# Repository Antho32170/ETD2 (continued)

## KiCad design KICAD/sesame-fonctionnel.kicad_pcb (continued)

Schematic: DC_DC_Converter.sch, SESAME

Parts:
C36, C37, C38, C47, C48, C49: 470uF; CP_Radial_D12.5mm_P5.00mm
C39, C40, C41, C42, C43, C44, C45, C46: C; C_0805_2012Metric_Pad1.18x1.45mm_HandSolder
L2: INDUCTOR; Multi-coil
QLP1: TK65G10N1; TO-263-2
QLS1: TK65G10N1; TO-263-2
QRP1: TK65G10N1; TO-263-2
QRS1: TK65G10N1; TO-263-2
R89, R90, R91, R92, R93, R94, R95, R96: R; R_0805_2012Metric_Pad1.20x1.40mm_HandSolder

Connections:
/DC/DC CONVERTER/VD_LS: C36.1, C37.1, C38.1, C39.1, C40.1, C41.1, QLS1.2 (D); also elsewhere on the board
/DC/DC CONVERTER/VG_LP: QLP1.1 (G), R90.1; also elsewhere on the board
/DC/DC CONVERTER/VG_LS: QLS1.1 (G), R89.1; also elsewhere on the board
/DC/DC CONVERTER/VG_RP: QRP1.1 (G), R96.1; also elsewhere on the board
/MOS DRIVER L/VS: C42.1, L2.1, QLP1.2 (D), QLS1.3 (S), R89.2, R91.2; also elsewhere on the board
/MOS DRIVER R/VG_P: QRS1.1 (G), R95.1; also elsewhere on the board
/MOS DRIVER R/VS: C44.1, L2.2, QRP1.2 (D), QRS1.3 (S), R93.2, R95.2; also elsewhere on the board
/U/I SENSOR RIGHT/VD_Mos: C43.1, C45.1, C46.1, C47.1, C48.1, C49.1, QRS1.2 (D); also elsewhere on the board
unnamed: C41.2, R91.1
unnamed: C42.2, R92.1
unnamed: C43.2, R93.1
unnamed: C44.2, R94.1

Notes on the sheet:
Inductor between 90uH -> 125uH https://fr.rs-online.com/web/p/inductances-traversantes/1816037 https://fr.rs-online.com/web/p/inductances-traversantes/1542466 https://fr.rs-online.com/web/p/inductances-traversantes/1048448 https://fr.rs-online.com/web/p/inductances-traversantes/1229231

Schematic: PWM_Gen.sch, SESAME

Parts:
C26: 100n; C_0805_2012Metric_Pad1.18x1.45mm_HandSolder
JP15, JP16, JP17, JP18: Jumper_3_Bridged12; SolderJumper-3_P1.3mm_Bridged12_Pad1.0x1.5mm
R70, R72, R73, R74, R75: 100k; R_0805_2012Metric_Pad1.20x1.40mm_HandSolder
R71: 4.7k; R_0805_2012Metric_Pad1.20x1.40mm_HandSolder
TP35: TP_NOP; TestPoint_THTPad_D2.0mm_Drill1.0mm
TP36, TP37, TP38: TP_POP; TestPoint_Loop_D1.80mm_Drill1.0mm_Beaded
U1, U13: AD8030; SO-8_5.3x6.2mm_P1.27mm

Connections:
/INT_PWM_Power: JP17.2 (C); also elsewhere on the board
/PID/Feedback: JP15.3 (B), JP16.1 (A), R73.2; also elsewhere on the board
/PWM GEN/Feedback_Deadtime: JP15.1 (A), JP16.3 (B), R75.2, TP36.1, U1.7
/PWM GEN/Feedback_Deadtime_Jump: JP15.2 (C), U13.3 (+)
/PWM GEN/Feedback_Jump: JP16.2 (C), U13.6 (-)
/PWM GEN/PWM_Power_Jumper: JP17.1 (A), JP18.3 (B), TP37.1, U13.1
/PWM GEN/Ramp: U13.2 (-), U13.5 (+); also elsewhere on the board
/PWM GEN/VDeadTime: R70.2, R71.1, R72.1, TP35.1
/PWM GEN/~PWM_Freewheel_Jumper: JP17.3 (B), JP18.1 (A), TP38.1, U13.7
/~INT_PWM_Freewheel: JP18.2 (C); also elsewhere on the board
unnamed: R72.2, R75.1, U1.6 (-)
unnamed: R73.1, R74.1, U1.5 (+)
VCC: C26.1, U13.8 (V+); also elsewhere on the board
VREF: R70.1; also elsewhere on the board

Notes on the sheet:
Deadtime on Feedback
Deadtime Voltage (270mV)
(V higher = More deadtime)
Gen. PWM_Power & ~PWM_Freewheel
Same IC package as the Feedback block
OP Amp supply
Deadtime ≃ 130 ns
TS3702 Comp push-pull

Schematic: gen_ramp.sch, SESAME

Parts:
C17: 100n; C_0805_2012Metric_Pad1.18x1.45mm_HandSolder
C18: 2.2n; C_0805_2012Metric_Pad1.18x1.45mm_HandSolder
R37, R40: 10k; R_0805_2012Metric_Pad1.20x1.40mm_HandSolder
R38: 11k; R_0805_2012Metric_Pad1.20x1.40mm_HandSolder
R39: 6.8k; R_0805_2012Metric_Pad1.20x1.40mm_HandSolder
R41: 13k; R_0805_2012Metric_Pad1.20x1.40mm_HandSolder
R42: 18k; R_0805_2012Metric_Pad1.20x1.40mm_HandSolder
R43: 680; R_0805_2012Metric_Pad1.20x1.40mm_HandSolder
TP18: TP_NOP; TestPoint_THTPad_D2.0mm_Drill1.0mm
TP19: TP_POP; TestPoint_Loop_D1.80mm_Drill1.0mm_Beaded
U7: AD8030; SO-8_5.3x6.2mm_P1.27mm

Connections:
/PWM GEN/Ramp: C18.1, R39.2, TP19.1, U7.7; also elsewhere on the board
/RAMP GENERATOR/Schmitt_offset: R37.1, R38.2, U7.2 (-)
/RAMP GENERATOR/Triangle_offset: R41.1, R42.2, U7.5 (+)
unnamed: C18.2, R43.1, U7.6 (-)
unnamed: R39.1, R40.2, U7.3 (+)
unnamed: R40.1, R43.2, TP18.1, U7.1
VCC: C17.1, U7.8 (V+); also elsewhere on the board
VREF: R37.2, R41.2; also elsewhere on the board

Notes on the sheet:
Integrateur
Schmitt trigger
Triangle offset (3.5V)
OP Amp supply
Schmitt tigger Offset (3.14V)
ponts diviseurs sur +7V ?

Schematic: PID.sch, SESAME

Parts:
C1: 100n; C_0805_2012Metric_Pad1.18x1.45mm_HandSolder
C2: NC; C_0805_2012Metric_Pad1.18x1.45mm_HandSolder
C3: 470n; C_0805_2012Metric_Pad1.18x1.45mm_HandSolder
C4: 22n; C_0805_2012Metric_Pad1.18x1.45mm_HandSolder
C5: 220n; C_0805_2012Metric_Pad1.18x1.45mm_HandSolder
D1: BZX384B5V1; D_SOD-323_HandSoldering
JP1, JP2, JP3: Jumper; PinHeader_1x02_P2.54mm_Vertical
R1, R2, R7: 10k; R_0805_2012Metric_Pad1.20x1.40mm_HandSolder
R3, R4, R5: 47k; R_0805_2012Metric_Pad1.20x1.40mm_HandSolder
R6: NC; R_0805_2012Metric_Pad1.20x1.40mm_HandSolder
R8: 20k; R_0805_2012Metric_Pad1.20x1.40mm_HandSolder
R9: 390; R_0805_2012Metric_Pad1.20x1.40mm_HandSolder
RV1: 10K; Potentiometer_Bourns_3214W_Vertical
TP2, TP4: TP_POP; TestPoint_Loop_D1.80mm_Drill1.0mm_Beaded
TP3: TP_NOP; TestPoint_THTPad_D2.0mm_Drill1.0mm
U1: AD8030; SO-8_5.3x6.2mm_P1.27mm

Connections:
/Ext_Setpoint: R5.2; also elsewhere on the board
/MEASURE SELECTOR/Measure_Selected: R6.2, R7.2; also elsewhere on the board
/PID/Feedback: D1.1 (K), R9.1, TP4.1; also elsewhere on the board
/PID/Feedback_raw: C4.1, C5.1, R9.2, TP3.1, U1.1
/PID/PID_Setpoint: C3.1, JP1.2, JP2.2, JP3.2, TP2.1, U1.3 (+)
unnamed: C2.1, C4.2, R7.1, R8.2, U1.2 (-)
unnamed: C2.2, R6.1
unnamed: C5.2, R8.1
unnamed: JP1.1, R3.1
unnamed: JP2.1, R4.1
unnamed: JP3.1, R5.1
unnamed: R1.2, R2.1, R4.2
unnamed: R3.2, RV1.2
VCC: C1.1, U1.8 (V+); also elsewhere on the board
VREF: R1.1, RV1.1; also elsewhere on the board

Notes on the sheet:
PID correction
Clamping 5.1V
OP Amp supply
Internal Setpoint Potentiometer
Internal Setpoint Voltage divider (3.5V)
23ms

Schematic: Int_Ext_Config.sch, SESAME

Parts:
J9: Conn_02x16_Odd_Even; PinSocket_2x16_P2.54mm_Vertical
JP10, JP11, JP12, JP13, JP14: Jumper_NC_Dual; PinHeader_1x03_P2.54mm_Vertical
R76, R77, R78: 10k; R_0805_2012Metric_Pad1.20x1.40mm_HandSolder

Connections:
/CC_CV_Mode: J9.18, R78.2; also elsewhere on the board
/Current_Sens_L: J9.10; also elsewhere on the board
/Current_Sens_R: J9.8; also elsewhere on the board
/Current_Thres: J9.26; also elsewhere on the board
/Dir: J9.16, R77.2; also elsewhere on the board
/Ext_Setpoint: J9.24; also elsewhere on the board
/INT EXT CONFIG/Ext_PWM: J9.30, JP10.3
/INT EXT CONFIG/~Ext_PWM: J9.32, JP11.3
/INT_PWM_Power: JP10.1; also elsewhere on the board
/Mode: J9.20, R76.2; also elsewhere on the board
/PWM_Power: JP10.2; also elsewhere on the board
/Rearm: J9.22; also elsewhere on the board
/Voltage_Sens_L: J9.14; also elsewhere on the board
/Voltage_Sens_R: J9.12; also elsewhere on the board
/Voltage_Thres: J9.28; also elsewhere on the board
/~INT_PWM_Freewheel: JP11.1; also elsewhere on the board
/~PWM_Freewheel: JP11.2; also elsewhere on the board
unnamed: JP12.2, R76.1
unnamed: JP13.2, R77.1
unnamed: JP14.2, R78.1
VCC: J9.2, J9.4, JP12.3, JP13.3, JP14.3; also elsewhere on the board
VREF: J9.6; also elsewhere on the board

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
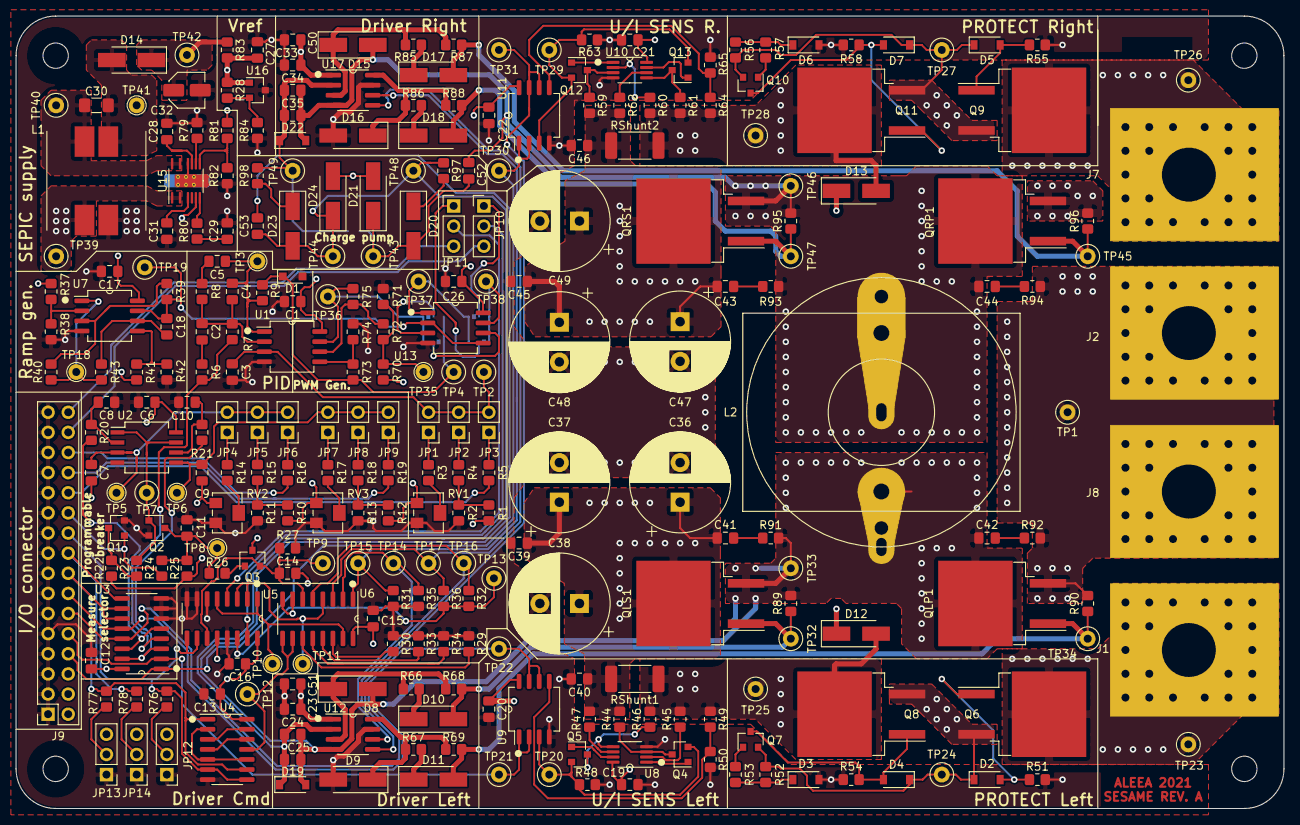
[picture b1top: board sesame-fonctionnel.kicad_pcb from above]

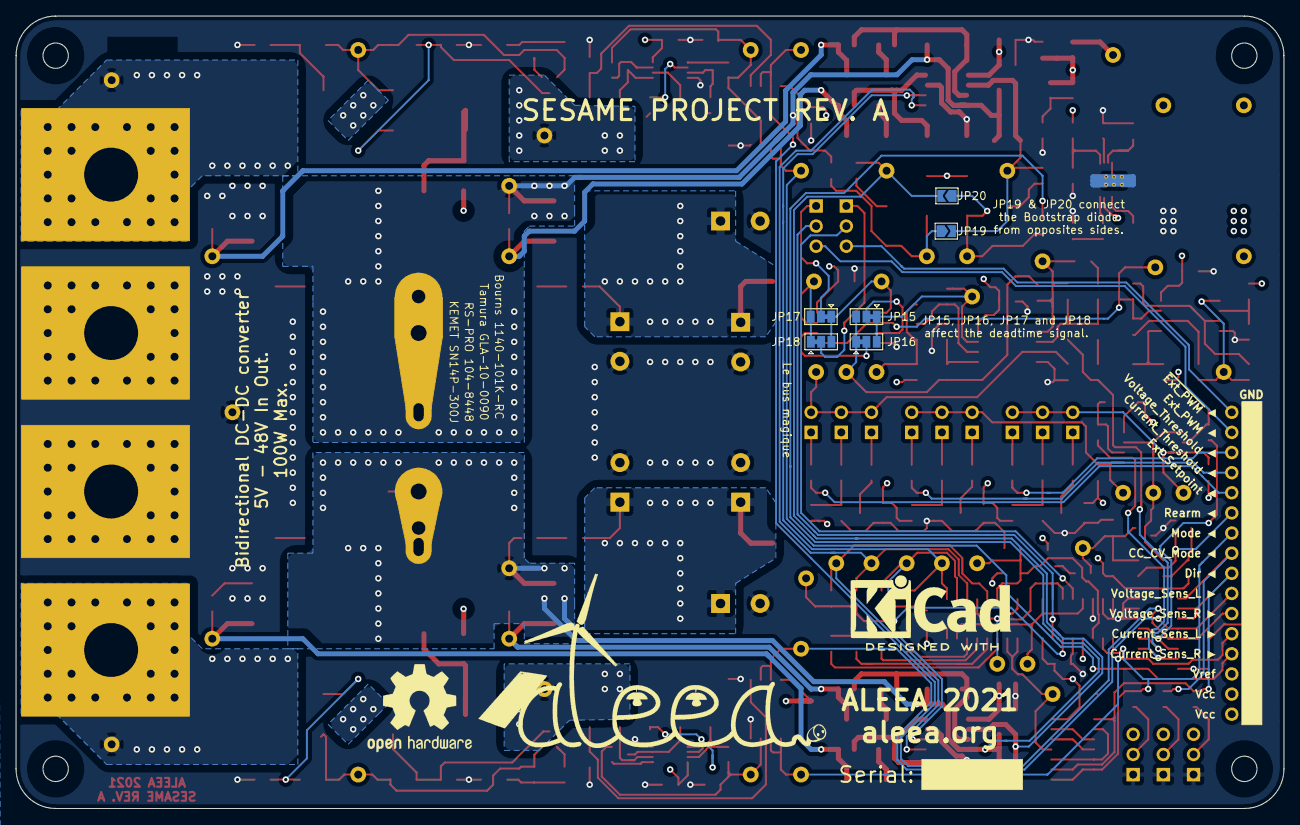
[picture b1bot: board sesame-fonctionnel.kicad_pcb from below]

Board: 4 copper layers, 160.0 x 100.0 mm, 293 parts (6 on the bottom side), 151 nets.

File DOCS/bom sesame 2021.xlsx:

Reference | Quantity | Value | Footprint | Datasheet | Manifacturer_Ref | Mouser | Conrad | Farnell | Digikey
C18 | 1 | 2.2n | Sesame_footprint:C_0805_2012Metric_Pad1.18x1.45mm_HandSolder | ~
C2 | 1 | NC | Sesame_footprint:C_0805_2012Metric_Pad1.18x1.45mm_HandSolder | ~
C25 C35 C52 C53 | 4 | 1u | Sesame_footprint:C_0805_2012Metric_Pad1.18x1.45mm_HandSolder | ~
C28 C29 C31 C39 C40 C41 C42 C43 C44 C45 C46 | 11 | C | Sesame_footprint:C_0805_2012Metric_Pad1.18x1.45mm_HandSolder | ~
C30 | 1 | 10u | Capacitor_SMD:C_1206_3216Metric_Pad1.42x1.75mm_HandSolder | ~
C32 | 1 | CP | Capacitor_SMD:C_Elec_4x5.8 | ~
C4 | 1 | 22n | Sesame_footprint:C_0805_2012Metric_Pad1.18x1.45mm_HandSolder | ~
C36 C37 C38 C47 C48 C49 | 6 | 470uF | Capacitor_THT:CP_Radial_D12.5mm_P5.00mm | ~
C5 | 1 | 220n | Sesame_footprint:C_0805_2012Metric_Pad1.18x1.45mm_HandSolder | ~
C50 C51 | 2 | 1uF | Sesame_footprint:C_0805_2012Metric_Pad1.18x1.45mm_HandSolder | ~
C1 C6 C12 C13 C15 C16 C17 C19 C20 C21 C22 C23 C24 C26 C27 C33 C34 | 17 | 100n | Sesame_footprint:C_0805_2012Metric_Pad1.18x1.45mm_HandSolder | ~
C3 C7 C9 C14 | 4 | 470n | Sesame_footprint:C_0805_2012Metric_Pad1.18x1.45mm_HandSolder | ~
C8 C10 C11 | 3 | 10n | Sesame_footprint:C_0805_2012Metric_Pad1.18x1.45mm_HandSolder | ~
D1 | 1 | BZX384B5V1 | Diode_SMD:D_SOD-323_HandSoldering | ~
D2 D4 D5 D7 D19 D22 | 6 | MMSZ5245 | Diode_SMD:D_SOD-123 | https://docs.rs-online.com/0640/0900766b814f560f.pdf
D3 D6 | 2 | MMSZ5262 | Diode_SMD:D_SOD-123 | https://docs.rs-online.com/0640/0900766b814f560f.pdf
D8 D9 D10 D11 D12 D13 D14 D15 D16 D17 D18 D20 D21 D23 D24 | 15 | SS36 | Diode_SMD:D_SMA_Handsoldering | ~
H1 H2 H3 H4 | 4 | MountingHole | Sesame_footprint:MountingHole_3.2mm_M3 | ~
J1 J2 J7 J8 | 4 | CXS70-14-C | Sesame_footprint:CXS70-14-C | ~
J9 | 1 | Conn_02x16_Odd_Even | Connector_PinSocket_2.54mm:PinSocket_2x16_P2.54mm_Vertical | ~
JP10 JP11 JP12 JP13 JP14 | 5 | Jumper_NC_Dual | Connector_PinHeader_2.54mm:PinHeader_1x03_P2.54mm_Vertical | ~
JP15 JP16 JP17 JP18 | 4 | Jumper_3_Bridged12 | Jumper:SolderJumper-3_P1.3mm_Bridged12_Pad1.0x1.5mm | ~
JP19 JP20 | 2 | Jumper_2_Open | Jumper:SolderJumper-2_P1.3mm_Open_TrianglePad1.0x1.5mm | ~
JP1 JP2 JP3 JP4 JP5 JP6 JP7 JP8 JP9 | 9 | Jumper | Connector_PinHeader_2.54mm:PinHeader_1x02_P2.54mm_Vertical | ~
L1 | 1 | L_Core_Ferrite_Coupled_2_Parts | Sesame_footprint:WE-DD_1260_128012
L2 | 1 | INDUCTOR | Sesame_footprint:Multi-coil | ~
Q1 Q2 Q3 Q4 Q5 Q12 Q13 | 7 | BC847 | Package_TO_SOT_SMD:SOT-23 | http://www.infineon.com/dgdl/Infineon-BC847SERIES_BC848SERIE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
Q6 Q8 Q9 Q11 | 4 | SQM120 | Package_TO_SOT_SMD:TO-263-2 | https://www.mouser.fr/datasheet/2/427/sqm120p10-10m1l-1766828.pdf
Q7 Q10 | 2 | BC857 | Package_TO_SOT_SMD:SOT-23 | https://www.onsemi.com/pub/Collateral/BC860-D.pdf
QLS1 QLP1 QRP1 QRS1 | 4 | TK65G10N1 | Package_TO_SOT_SMD:TO-263-2 | https://docs.rs-online.com/a1f4/0900766b816230a5.pdf
R10 R11 R12 R13 R80 R89 R90 R91 R92 R93 R94 R95 R96 | 13 | R | Sesame_footprint:R_0805_2012Metric_Pad1.20x1.40mm_HandSolder | ~
R14 R15 R16 R17 R18 R19 R20 R21 R52 R53 R56 R57 R70 R72 R73 R74 R75 | 17 | 100k | Sesame_footprint:R_0805_2012Metric_Pad1.20x1.40mm_HandSolder | ~
R3 R4 R5 R22 R23 R24 R25 R27 | 8 | 47k | Sesame_footprint:R_0805_2012Metric_Pad1.20x1.40mm_HandSolder | ~
R1 R2 R7 R26 R29 R30 R31 R32 R35 R36 R37 R40 R50 R65 R76 R77 R78 R84 R97 R98 | 20 | 10k | Sesame_footprint:R_0805_2012Metric_Pad1.20x1.40mm_HandSolder | ~
R28 | 1 | 14k | Sesame_footprint:R_0805_2012Metric_Pad1.20x1.40mm_HandSolder | ~
R6 R33 R34 | 3 | NC | Sesame_footprint:R_0805_2012Metric_Pad1.20x1.40mm_HandSolder | ~
R38 | 1 | 11k | Sesame_footprint:R_0805_2012Metric_Pad1.20x1.40mm_HandSolder | ~
R39 | 1 | 6.8k | Sesame_footprint:R_0805_2012Metric_Pad1.20x1.40mm_HandSolder | ~
R41 | 1 | 13k | Sesame_footprint:R_0805_2012Metric_Pad1.20x1.40mm_HandSolder | ~
R42 | 1 | 18k | Sesame_footprint:R_0805_2012Metric_Pad1.20x1.40mm_HandSolder | ~
R43 | 1 | 680 | Sesame_footprint:R_0805_2012Metric_Pad1.20x1.40mm_HandSolder | ~
R44 R45 R46 R47 R59 R60 R61 R62 R83 | 9 | 200 | Sesame_footprint:R_0805_2012Metric_Pad1.20x1.40mm_HandSolder | ~
R8 R48 R63 | 3 | 20k | Sesame_footprint:R_0805_2012Metric_Pad1.20x1.40mm_HandSolder | ~
R49 R64 | 2 | 90k | Sesame_footprint:R_0805_2012Metric_Pad1.20x1.40mm_HandSolder | ~
R51 R55 | 2 | 330k | Sesame_footprint:R_0805_2012Metric_Pad1.20x1.40mm_HandSolder | ~
R54 R58 R81 | 3 | 1M | Sesame_footprint:R_0805_2012Metric_Pad1.20x1.40mm_HandSolder | ~
R66 R67 R85 R86 | 4 | 1 | Sesame_footprint:R_0805_2012Metric_Pad1.20x1.40mm_HandSolder | ~
R68 R69 R87 R88 | 4 | 5 | Sesame_footprint:R_0805_2012Metric_Pad1.20x1.40mm_HandSolder | ~
R71 | 1 | 4.7k | Sesame_footprint:R_0805_2012Metric_Pad1.20x1.40mm_HandSolder | ~
R79 | 1 | 84.5 | Sesame_footprint:R_0805_2012Metric_Pad1.20x1.40mm_HandSolder | ~
R82 | 1 | 296k | Sesame_footprint:R_0805_2012Metric_Pad1.20x1.40mm_HandSolder | ~
R9 | 1 | 390 | Sesame_footprint:R_0805_2012Metric_Pad1.20x1.40mm_HandSolder | ~
RShunt1 RShunt2 | 2 | PA2512FKF070R005E | Resistor_SMD:R_2512_6332Metric_Pad1.52x3.35mm_HandSolder | ~
RV1 RV2 RV3 | 3 | 10K | Potentiometer_SMD:Potentiometer_Bourns_3214W_Vertical | https://docs.rs-online.com/0467/0900766b80025f51.pdf | 3214W
TP1 TP2 TP4 TP7 TP9 TP12 TP13 TP14 TP15 TP16 TP17 TP19 TP20 TP21 TP22 TP23 TP24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 | 40 | TP_POP | TestPoint:TestPoint_Loop_D1.80mm_Drill1.0mm_Beaded | ~
TP3 TP5 TP6 TP8 TP10 TP11 TP18 TP35 TP41 | 9 | TP_NOP | TestPoint:TestPoint_THTPad_D2.0mm_Drill1.0mm | ~
U12 U17 | 2 | UCC27284-Q1 | Sesame_footprint:SOIC-8_3.9x4.9mm_P1.27mm
U15 | 1 | LT8365 | Sesame_footprint:MSE-16-1EP_3x4mm_P0.5mm_EP1.65x2.85mm_ThermalVias
U16 | 1 | TL431DBZ | Package_TO_SOT_SMD:SOT-23 | http://www.ti.com/lit/ds/symlink/tl431.pdf
U2 | 1 | LM2903 | Package_SO:SO-8_5.3x6.2mm_P1.27mm | http://www.ti.com/lit/ds/symlink/lm393.pdf
U3 U5 U6 | 3 | CD4053BM96 | Sesame_footprint:SOIC-16_3.9x9.9mm_P1.27mm | http://www.ti.com/lit/ds/symlink/cd4052b.pdf
U4 | 1 | 4011 | Sesame_footprint:SOIC-14_3.9x8.7mm_P1.27mm | http://www.intersil.com/content/dam/Intersil/documents/cd40/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
U8 U10 | 2 | LT6016 | Sesame_footprint:MSOP-8_3x3mm_P0.65mm
U1 U7 U9 U11 U13 | 5 | AD8030 | Sesame_footprint:SO-8_5.3x6.2mm_P1.27mm

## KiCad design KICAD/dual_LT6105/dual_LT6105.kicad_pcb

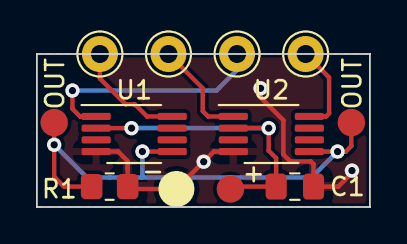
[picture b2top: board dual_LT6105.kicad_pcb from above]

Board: 2 copper layers, 18.5 x 8.5 mm, 12 parts (0 on the bottom side), 7 nets.

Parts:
+: Conn_01x01; conn_pad
-: Conn_01x01; conn_pad
C1: 100n; C_0805_2012Metric_Pad1.18x1.45mm_HandSolder
J3, J4, J5, J6: Conn_01x01; Pin_D1.0mm_L10.0mm
OUT: Conn_01x01; conn_pad
OUT#2: Conn_01x01; conn_pad
R1: 20k; R_0805_2012Metric_Pad1.20x1.40mm_HandSolder
U1, U2: LT6105; MSOP-8_3x3mm_P0.65mm

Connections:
GND: -.1, C1.2, R1.2, U1.4 (V-), U2.4 (V-)
unnamed: J3.1, U1.8 (+)
unnamed: J4.1, U1.1 (-)
unnamed: J5.1, U2.8 (+)
unnamed: J6.1, U2.1 (-)
unnamed: OUT.1, OUT#2.1, R1.1, U1.5, U2.5
VCC: +.1, C1.1, U1.2 (V+), U2.2 (V+)

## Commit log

2021-08-02 Feuilles hierachiques terminees
2021-08-02 cleanup
2021-08-03 removed legacy symbols
2021-08-03 labels dans les blocks
2021-08-03 add 4053
2021-08-03 Maj auto
2021-08-03 modif cartouche
2021-08-03 fix rescue symbol
2021-08-03 finished measure selector
2021-08-05 Nearly finished Driver cmd
2021-08-05 added sim for open collector opamp. and new breaker
2021-08-05 update header + redraw Driver CMD
2021-08-06 changed grid for Measure selector
2021-08-06 added ina240 sim + drawed protect and DC-DC chopper
2021-08-07 added ramp draed by jebin + mod the current sim and it's working
    !
2021-08-08 mod the main sheet + drawed the first full version of the u/i sensor
2021-08-15 minors edits + 7v rail
2021-08-15 ebauche driver mos
2021-08-15 added draft pwm gen & pid
2021-08-17 a ton of new stuff. V0.8
2021-08-19 alim sepic sim + diff mos sim
2021-08-20 simu meseure de courant sans sommateur
2021-08-20 current measure new style sim
2021-08-21 PID + PWM + RAMP finished
2021-08-21 reworked driver command
2021-08-22 worked on power supply + connectors
2021-08-22 added footprint lib + steps for connectors
2021-08-22 moved things arround in the main sheet
2021-08-22 lt6015 it is
2021-08-23 mainly footprints
2021-08-23 revex with jmt
2021-08-23 minor cleanup
2021-08-23 Stef merge
2021-08-23 drivers draft + clean and minors changes
2021-08-24 driver + clean clean clean
2021-08-24 review w/ jmt
2021-08-24 edit footprints by jmt
2021-08-25 route + work on djd
2021-08-25 added footprint for sepic coil + no more errors in netlist
2021-08-25 added footprint sepic + place place place
2021-08-26 end of placement 7 beginning of routing
2021-08-27 changed monting holes + tweaks & still routing
2021-08-27 protect left finished
2021-08-27 changed transistor placement in protect
2021-08-27 little cleanup. 278 conn. to go
2021-08-27 clean up eco user 2 layer
2021-08-27 protect right. 249 conn.
2021-08-28 200 conn. remaining
2021-08-28 ui sens right. 170 conn.
2021-08-28 right driver done. 149 conn.
2021-08-28 144 conn. will convert to 4 layers
2021-08-28 test w/ layers indicator
2021-08-28 layer indicator stuff
2021-08-29 95 conn. doing analog switchs
2021-08-29 63 conn. dij placed
2021-08-29 30 conn. changed again the pinout of io connector
2021-08-29 all done. 3 conn. left for vref
2021-08-29 ibom for testing
2021-08-30 changed ground planes
2021-08-30 enhanced copper planes
2021-08-30 sim vref + djd write
2021-08-30 0 conn. + new vref
2021-08-30 correction on the ext config
2021-08-30 simu vref + djd vref
2021-08-30 mod. ref rail on kicad
2021-08-31 minor changes on the bottom layer + minor silkscreen cleaning
2021-09-02 cleanup silkscreen
2021-09-02 lil cleanup silk and gate tracks
2021-09-02 clean clean clean. still not finished '
2021-09-02 modified deadtime + added config pads on the bottom for charge pump config
2021-09-03 minor changes
2021-09-19 lil cleanup on the main schematic sheet
2021-09-19 fixed a mistake w/ not connected net and net naming mistake
2021-09-23 V1.0 of the schematic
2021-09-24 fab files rev A
2021-10-01 drill plan
2021-10-01 project save
2021-11-09 \added dual lt1605
2021-11-26 added gitignore and docs need cleenup
2021-11-26 export the dual LT6105 board
2021-12-02 procedure de montage du dual lt6105
2021-12-16 added datasheets + test bench first version
2021-12-20 refactor code tester. not tested
2021-12-20 small fix
2021-12-21 new mult tester
2021-12-21 fix the escort dmm reading
2021-12-21 working git add imgs/
2021-12-24 curves network
2021-12-25 working multilines tracer
2022-09-19 Delete TESTS directory
    moved in a separate git
2022-12-15 /test
    test
2022-12-15 Create CDC & Exigences
2022-12-15 Create Exigences & CDC
2022-12-15 Exigences & CDC
